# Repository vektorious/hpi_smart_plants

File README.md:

# Smart Plants Starter Kit

A hands-on introduction to building low-power, Wi-Fi-connected plant monitoring systems.
You'll learn the basics of microcontroller programming, soil moisture sensing, and Wi-Fi data
transfer — all while building a device that actually keeps your plants alive.

The device wakes from deep sleep, reads soil moisture (and optionally temperature, humidity,
light, and battery level), sends data to an online dashboard, then sleeps again to conserve
battery.

---

## What You'll Build

By the end of the workshop you'll have a battery-powered soil moisture sensor that:
- Measures soil moisture every hour (configurable)
- Sends data to an online dashboard via Wi-Fi
- Sleeps between measurements to conserve battery
- Waters your plant automatically when the soil gets too dry

No soldering experience required — but you'll get the chance to try!

---

## What's in the Kit

- Waveshare ESP32-C6 Zero microcontroller
- Smart Plants breakout PCB
- Capacitive soil moisture sensor + cable
- BME280 sensor (temperature, humidity, pressure)
- TSL2591 sensor (light)
- Mini diaphragm pump
- Battery pack
- Laser-cut housing
- 3D-printed sensor and pump housings
- Screws, velcro, cable gland

---

## Before You Begin

Make sure you have:
- A computer with a USB-C port (or adapter) and a **Chrome, Edge, or Opera** browser
  (used by the browser-based firmware installer)
- A USB-C **data** cable
- A 2.4 GHz Wi-Fi network

Everything else — firmware and configuration — is covered step by step in the build instructions
below. You install the firmware straight from the browser; only building it from source needs the
[Arduino IDE](https://www.arduino.cc/en/software).

---

## Build Instructions

**Start here:** [`instructions/build_instructions.md`](instructions/build_instructions.md)

That guide covers the full assembly, programming, calibration, and deployment for the main
Waveshare build — from soldering the PCB to seeing your first readings on the dashboard.

Firmware installs from the browser — no toolchain needed — via the web flasher:
**<https://vektorious.github.io/hpi_smart_plants/>**.

---

## Learning Goals

- Read analog sensor data and convert it to meaningful values
- Understand how to minimise power consumption with deep sleep
- Send data securely to a server over Wi-Fi using HTTP
- Learn how a cloud dashboard receives and displays live sensor readings

---

## Configured on the Device

All per-device settings — Wi-Fi, device name, sleep interval, moisture calibration, and
which sensors and the pump are enabled — are configured **on the device through a Wi-Fi setup
portal** after flashing, and stored in non-volatile memory. No code edits or recompiling: one
flashed binary works for every configuration.

The setup portal opens automatically on first boot (or on a double-press of the reset button) and
also shows **live sensor readings** and an **API connection test** so you can confirm everything
works. The `DEFAULT_*` values in `code/sp_modular/config.h` are only the factory defaults applied
on first boot. Building from source? See
[`instructions/firmware_from_source.md`](instructions/firmware_from_source.md).

---

## Board Variants

Two controller boards are supported. Both run the same firmware (`code/sp_modular/`).

| Variant | Board | PCB | Who it's for |
|---------|-------|-----|--------------|
| **Main build** | Waveshare ESP32-C6 Zero | `smart_plants_breakout_ws-board_rev2` | Student workshops |
| **Alternative** | SEEED Studio XIAO ESP32-C6 | `smart_plants_breakout_rev1` | Alternative / reference build |

---

## Repository Structure

```
code/
  sp_modular/              Modular firmware (current, for all builds)
    config.h               Factory defaults (DEFAULT_*), pin assignments, structs
    settings.ino           Runtime settings stored in NVS/Preferences
    portal.ino             WiFiManager setup portal + live sensor page
    sp_modular.ino         Entry point
    *.ino                  Sensor and actuator modules
  legacy/                  Old monolithic sketches (breadboard era, unsupported)

web-flasher/               Browser-based firmware installer (ESP Web Tools)

hardware/
  pcb/
    smart_plants_breakout_ws-board_rev2/   Main build PCB (Waveshare)
    smart_plants_breakout_rev1/            Alternative build PCB (XIAO)
    legacy/                                Older PCB revisions
    ext_files/                             KiCAD footprints and symbols
  3d-print/
    bme_housing/           Miniature Stevenson screen for BME280
    light_sensor/          TSL2591 mount with diffuser
    moisture_sensor/       Soil probe housing
    pump/                  Diaphragm pump enclosure
    cable_plugs/           M12 cable gland plug
  laser_files/
    SmartPlants_4mm_v3.svg Current enclosure template (4 mm material)
    legacy/                Older enclosure versions

instructions/
  build_instructions.md    Main build guide — start here
  firmware_from_source.md  Build/upload from Arduino IDE + component test sketches
  background_information.md Sensor theory, system overview, design rationale
  quick_reference/         Printable one-page build reference (md, html, pdf)
  legacy/                  Old breadboard-era guides (unsupported)

img/                       Photos and diagrams referenced by the instructions
```

---

## Background Reading

[`instructions/background_information.md`](instructions/background_information.md) covers:

- **Sensor selection** — why capacitive over resistive moisture sensors, why BME280 and TSL2591
  were chosen over simpler alternatives, and the trade-offs involved
- **Pump control** — how MOSFETs and relays work, and why this design uses an IRLZ14
- **How the system works** — the full data path from firmware wake-up cycle through the FastAPI
  server and PostgreSQL database to the live Grafana dashboard
- **Similar projects** — related open-source plant monitoring builds for further inspiration

Useful context for understanding *why* things are built the way they are.

---

## Licenses

| Component | License |
|-----------|---------|
| Software (`code/`) | [MIT](LICENSE.code) |
| Hardware (`hardware/`) | [CERN-OHL-W 2.0](LICENSE.hardware) |
| Documentation (`instructions/`, `README.md`, `img/`) | [CC-BY 4.0](LICENSE.docs) |

This project is certified open source hardware by OSHWA under certification ID `DE000173`.

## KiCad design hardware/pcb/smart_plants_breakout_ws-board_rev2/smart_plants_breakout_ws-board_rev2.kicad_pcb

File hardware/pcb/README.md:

# PCB Designs

Two active PCB designs are maintained, one per supported controller board. Both route sensors
to the same GPIO numbers, so no firmware changes are needed between variants.

## Active designs

### Waveshare ESP32-C6 Zero — `smart_plants_breakout_ws-board_rev2/` (main build)

The primary board used in student workshops. Designed for the
[Waveshare ESP32-C6 Zero](https://www.waveshare.com/wiki/ESP32-C6-Zero).

- **Gerber files:** `sp_ws_breakout_rev2/` folder and `sp_ws_breakout_rev2.zip`
- **KiCAD project:** `smart_plants_breakout_ws-board_rev2.kicad_pro`
- **Firmware pin config:** active block in `code/sp_modular/config.h`

### SEEED Studio XIAO ESP32-C6 — `smart_plants_breakout_rev1/` (alternative build)

Alternative build based on the [XIAO ESP32-C6](https://wiki.seeedstudio.com/xiao_esp32c6_getting_started/).

- **Gerber files:** `smart_plants_breakout_rev1_gerber/` folder and `smart_plants_breakout_rev1_gerber.zip`
- **KiCAD project:** `smart_plants_breakout_rev1.kicad_pro`
- **BOM:** `smart_plants_breakout_rev1.csv`
- **Firmware pin config:** see the commented-out XIAO block in `code/sp_modular/config.h` (TODO: GPIO numbers need to be verified)

## Ordering PCBs

1. Download the Gerber `.zip` file for your chosen variant.
2. Upload it to a PCB fab of your choice (e.g., JLCPCB, PCBWay, Aisler).
3. Default settings (1.6 mm FR4, 2 layers, HASL finish) work fine.

## Opening in KiCAD

Open the `.kicad_pro` file in KiCAD 8 or later. External footprint libraries are in
`ext_files/` — KiCAD will prompt you to resolve them on first open; point it to that folder.

## Legacy designs

Older PCB revisions are in `legacy/`. They are archived for reference only.

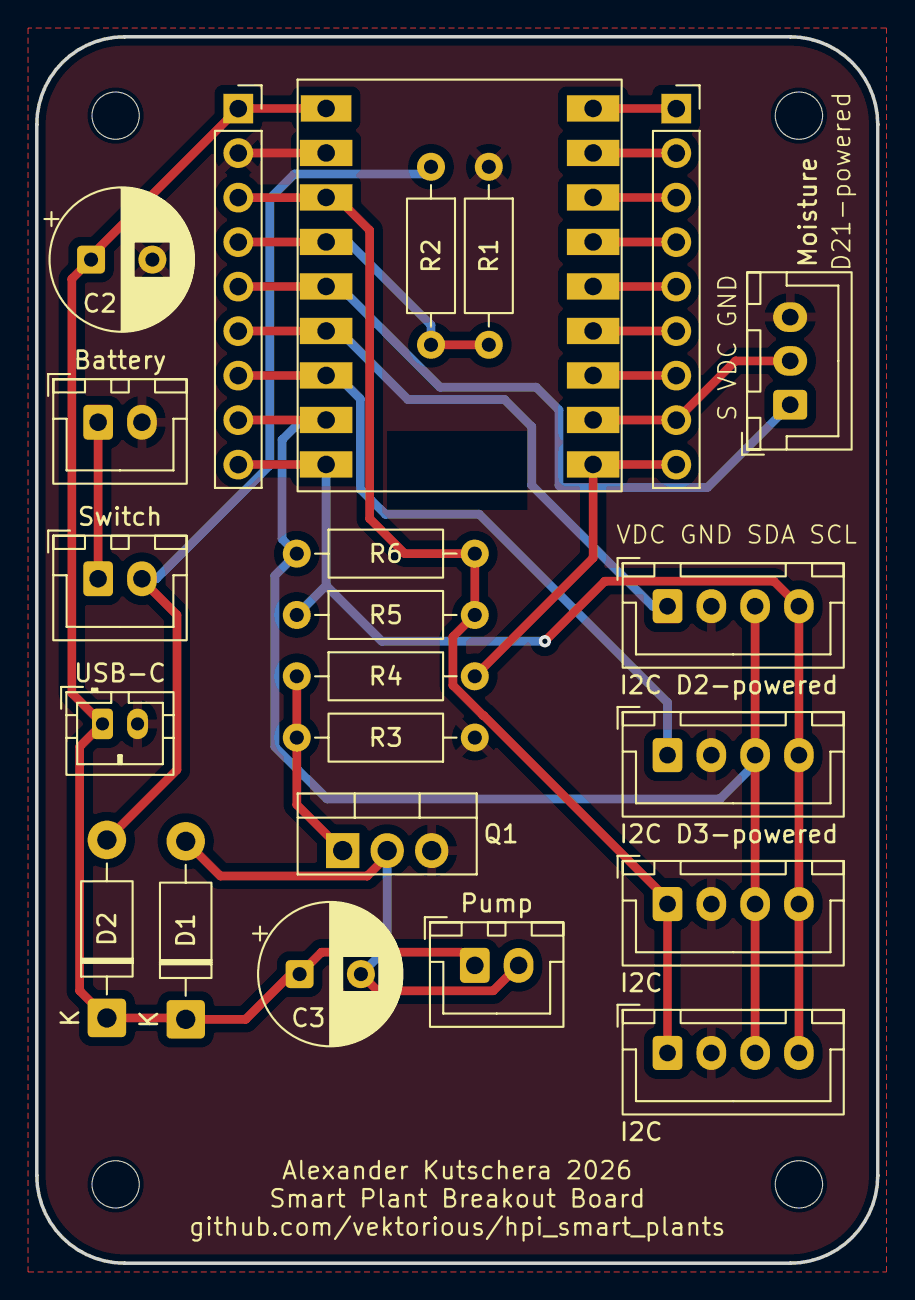
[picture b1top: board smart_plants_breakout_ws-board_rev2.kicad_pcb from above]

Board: 2 copper layers, 48.0 x 70.0 mm, 27 parts (0 on the bottom side), 22 nets.

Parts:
Battery: Battery; JST_XH_B2B-XH-A_1x02_P2.50mm_Vertical
C2: 220µF; CP_Radial_D8.0mm_P3.50mm
C3: 22µF; CP_Radial_D8.0mm_P3.50mm
D1: 1N4001; D_DO-41_SOD81_P10.16mm_Horizontal
D2: 1N5817; D_DO-41_SOD81_P10.16mm_Horizontal
H1, H2, H3, H4: MountingHole; MountingHole_2.7mm_M2.5
I2C, I2C#2: I2C; JST_XH_B4B-XH-A_1x04_P2.50mm_Vertical
I2C D2-powered: I2C D2-powered; JST_XH_B4B-XH-A_1x04_P2.50mm_Vertical
I2C D3-powered: I2C D3-powered; JST_XH_B4B-XH-A_1x04_P2.50mm_Vertical
J1, J2: Conn_01x09_Pin; PinSocket_1x09_P2.54mm_Vertical
Moisture: Moisture Sensor; JST_XH_B3B-XH-A_1x03_P2.50mm_Vertical
Pump: Pump; JST_XH_B2B-XH-A_1x02_P2.50mm_Vertical
Q1: IRLZ14; TO-220-3_Vertical
R1, R2: 220k; R_Axial_DIN0207_L6.3mm_D2.5mm_P10.16mm_Horizontal
R3: 10k; R_Axial_DIN0207_L6.3mm_D2.5mm_P10.16mm_Horizontal
R4: 22R; R_Axial_DIN0207_L6.3mm_D2.5mm_P10.16mm_Horizontal
R5, R6: 4k7; R_Axial_DIN0207_L6.3mm_D2.5mm_P10.16mm_Horizontal
Switch: Power Switch; JST_XH_B2B-XH-A_1x02_P2.50mm_Vertical
U1: Waveshare ESP32-C6-Nano; Waveshare-ESP32-C6-Zero-THT
USB-C: USB-C Power; JST_PH_B2B-PH-K_1x02_P2.00mm_Vertical

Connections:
GND: Battery.2, C2.2, I2C.2, I2C D2-powered.2, I2C D3-powered.2, I2C#2.2, J1.2, Moisture.3, Q1.3 (S), R1.1, R3.1, U1.2 (GND), USB-C.2
unnamed: C3.2, D1.2 (A), Pump.2, Q1.2 (D)
unnamed: C2.1, C3.1, D1.1 (K), D2.1 (K), J1.1, Pump.1, U1.1 (VCC), USB-C.1
unnamed: D2.2 (A), R2.1, Switch.2 (B)
unnamed: J1.4, R1.2, R2.2, U1.4 (IO0)
unnamed: J1.5, Moisture.1, U1.5 (IO1)
unnamed: I2C D2-powered.1, J1.6, U1.6 (IO2)
unnamed: I2C D3-powered.1, J1.7, U1.7 (IO3)
unnamed: I2C.3, I2C D2-powered.3, I2C D3-powered.3, I2C#2.3, J1.8, R6.1, U1.8 (IO4)
unnamed: I2C.4, I2C D2-powered.4, I2C D3-powered.4, I2C#2.4, J1.9, R5.1, U1.9 (IO5)
unnamed: J2.1, U1.18 (TX)
unnamed: J2.2, U1.17 (RX)
unnamed: J2.3, U1.16 (IO14)
unnamed: J2.4, U1.15 (IO15)
unnamed: J2.5, U1.14 (IO18)
unnamed: J2.6, U1.13 (IO19)
unnamed: J2.7, U1.12 (IO20)
unnamed: J2.8, Moisture.2, U1.11 (IO21)
unnamed: J2.9, R4.2, U1.10 (IO22)
unnamed: Battery.1, Switch.1 (A)
unnamed: Q1.1 (G), R3.2, R4.1
VDC: I2C.1, I2C#2.1, J1.3, R5.2, R6.2, U1.3 (V3V)

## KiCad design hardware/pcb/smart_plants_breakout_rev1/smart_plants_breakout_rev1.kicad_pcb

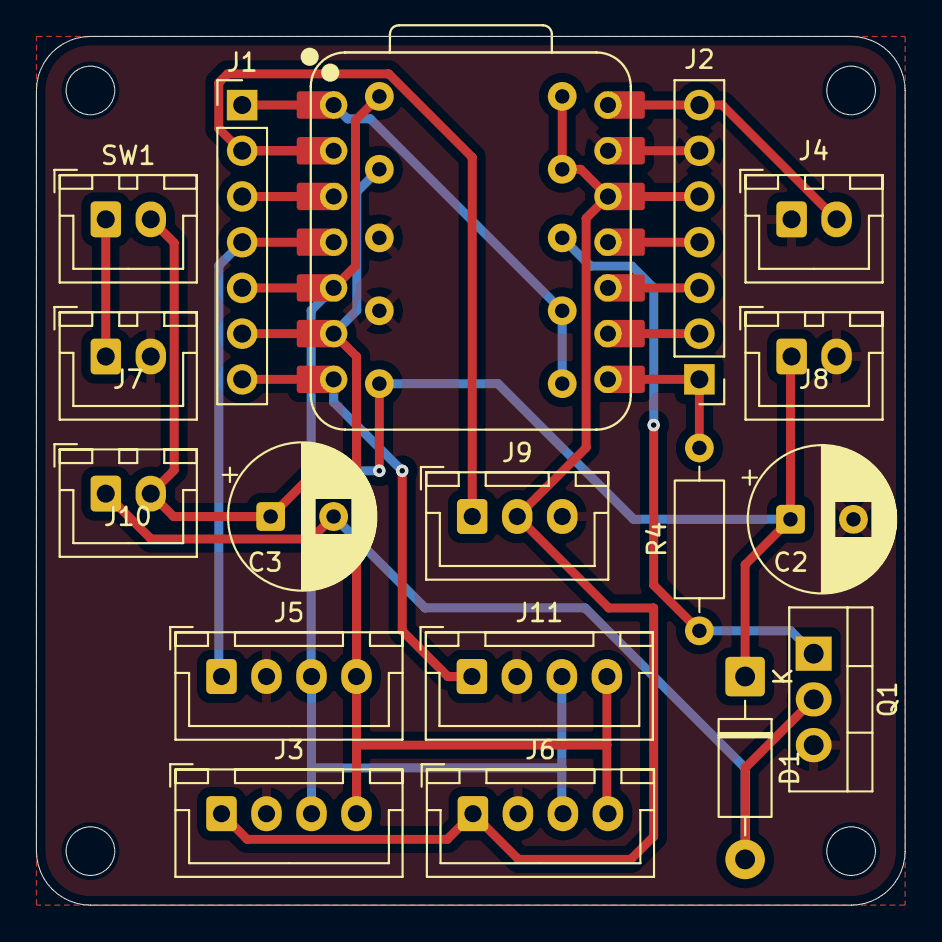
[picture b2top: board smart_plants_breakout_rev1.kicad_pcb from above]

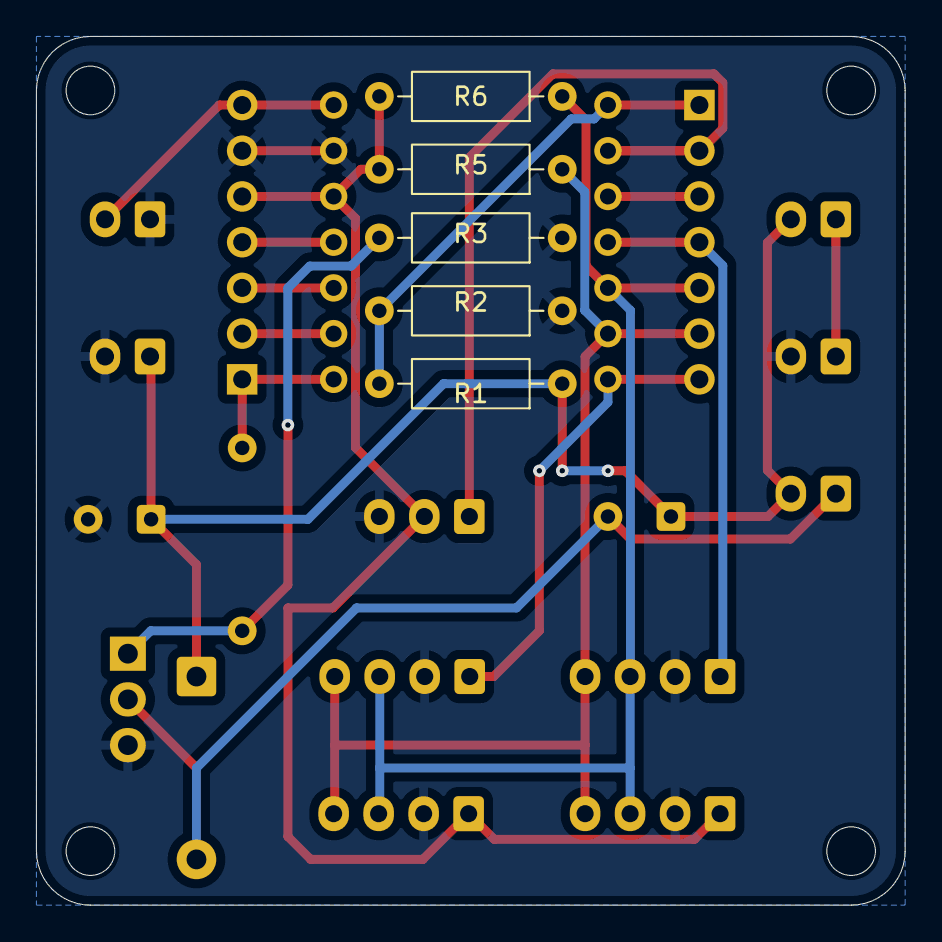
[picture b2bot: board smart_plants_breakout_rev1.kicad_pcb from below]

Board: 2 copper layers, 48.3 x 48.3 mm, 27 parts (5 on the bottom side), 18 nets.

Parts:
C2: 220µF; CP_Radial_D8.0mm_P3.50mm
C3: 22µF; CP_Radial_D8.0mm_P3.50mm
D1: 1N4001; D_DO-41_SOD81_P10.16mm_Horizontal
H1, H2, H3, H4: MountingHole; MountingHole_2.7mm_M2.5
J1, J2: Breakout; PinHeader_1x07_P2.54mm_Vertical
J3, J6: I2C; JST_XH_B4B-XH-A_1x04_P2.50mm_Vertical
J4: USB-C Power; JST_XH_B2B-XH-A_1x02_P2.50mm_Vertical
J5: I2C D3-powered; JST_XH_B4B-XH-A_1x04_P2.50mm_Vertical
J7: Battery; JST_XH_B2B-XH-A_1x02_P2.50mm_Vertical
J8: Board Power; JST_XH_B2B-XH-A_1x02_P2.50mm_Vertical
J9: Moisture Sensor; JST_XH_B3B-XH-A_1x03_P2.50mm_Vertical
J10: Pump; JST_XH_B2B-XH-A_1x02_P2.50mm_Vertical
J11: I2C D6-powered; JST_XH_B4B-XH-A_1x04_P2.50mm_Vertical
Q1: IRLZ14; TO-220-3_Vertical
R1, R2: 220k; R_Axial_DIN0207_L6.3mm_D2.5mm_P10.16mm_Horizontal
R3: 10k; R_Axial_DIN0207_L6.3mm_D2.5mm_P10.16mm_Horizontal
R4: 22R; R_Axial_DIN0207_L6.3mm_D2.5mm_P10.16mm_Horizontal
R5, R6: 4k7; R_Axial_DIN0207_L6.3mm_D2.5mm_P10.16mm_Horizontal
SW1: Power Switch; JST_XH_B2B-XH-A_1x02_P2.50mm_Vertical
U1: XIAO-ESP32-C6; XIAO-ESP32C6-DIP

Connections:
BAT+: C2.1, C3.1, D1.1 (K), J8.1, J10.2, R1.1, SW1.2 (B)
BAT-: C2.2, J2.6, J3.2, J4.1, J5.2, J6.2, J7.2, J8.2, J9.3, J11.2, Q1.3 (S), R2.1, R3.1, U1.13 (GND)
unnamed: C3.2, D1.2 (A), J10.1, Q1.2 (D)
unnamed: J1.1, R1.2, R2.2, U1.1 (GPIO0/A0/D0)
unnamed: J1.2, J9.1, U1.2 (GPIO1/A1/D1)
unnamed: J1.3, U1.3 (GPIO2/A2/D2)
unnamed: J1.4, J5.1, U1.4 (GPIO21/D3)
unnamed: J1.5, J3.3, J5.3, J6.3, J11.3, R6.1, U1.5 (GPIO22/D4/SDA)
unnamed: J1.6, J3.4, J5.4, J6.4, J11.4, R5.1, U1.6 (GPIO23/D5/SCL)
unnamed: J1.7, J11.1, U1.7 (GPIO16/D6/TX)
unnamed: J2.1, R4.2, U1.8 (GPIO17/D7/RX)
unnamed: J2.2, U1.9 (GPIO19/D8/SCK)
unnamed: J2.3, U1.10 (GPIO20/D9/MISO)
unnamed: J2.4, U1.11 (GPIO18/D10/MOSI)
unnamed: J7.1, SW1.1 (A)
unnamed: Q1.1 (G), R3.2, R4.1
VBUS: J2.7, J4.2, U1.14 (VBUS)
VDC: J2.5, J3.1, J6.1, J9.2, R5.2, R6.2, U1.12 (3V3)

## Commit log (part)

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2025-09-18 Adds build instructions and images
    Adds a comprehensive instructions document detailing the steps to assemble the moisture sensor project, including preparation, circuit assembly, programming, and final testing.
    Includes associated images for each step to aid visual understanding.
2025-09-18 Updates images and adds spacing for clarity
    Improves the visual presentation of the assembly instructions.
    Adds spacing between steps for better readability and increases the size of circuit diagrams for improved clarity.
2025-09-18 Refactors instructions for clarity.
    Improves the instructions document by:
    - Adjusting the formatting of image elements for better layout.
    - Restructuring titles for better organization and readability.
2025-09-18 Refractors instructions, adds ESP32 board pinout
2025-09-18 Adds initial project files and instructions
    Initializes the "Smart Plants Starter Kit" project with a README,
    instructions, and an image of the ESP32-C6 pinout.
    The project provides a hands-on introduction to building a low-power,
    Wi-Fi-connected plant monitoring system.
    Uses a local image for the ESP32-C6 pinout in the instructions.
2025-09-18 Uploaded first script
2025-09-23 Adds WiFi Manager for configuration
    Implements WiFi Manager to allow for easy configuration
    of the WiFi connection via a web interface if the device
    is unable to connect using the stored credentials.
    Also refactors the WiFi connection logic into its own function.
2025-09-24 Updated instructions
2025-11-18 Adds 3D-models
2025-11-18 Adds files for the laser cutter
2025-11-18 Adds PCB breakout design files
2025-11-18 fixed error in 3D-design
2025-11-18 Added code samples
2025-11-18 Fixed errors in the fritzing layouts and added new ones
2025-11-18 added circuit exports
2025-11-18 Added 3D-files and Attribution
2025-11-18 updated BOM
2025-11-18 updated img paths
2025-12-10 Added new code sketch
2026-03-06 Added PCB
2026-04-07 WS PCB bug fixes
2026-04-07 WS PCB rev2
2026-04-20 added new housing files
2026-04-22 minor improvements in housing files
2026-04-22 fix: apply code review improvements to sp_modular firmware
    - Remove hasAnyData guard that prevented data from being sent when
    optional sensors are disabled (#3)
    - Add moisture_voltage field to JSON payload (#9)
    - Power off BME280 and TSL2591 after reading to save battery (#4)
    - Move Wire.begin() to setup() and guard it with feature flags (#5)
    - Add warm-up ADC read for battery voltage to discard noisy first
2026-04-22 reodering 3D-print files
2026-04-22 moving light sensor file
2026-04-23 fix: send light sensor data when lux/IR are 0 at night
    calculateLux(0, 0) produced NaN due to internal division by zero,
    causing lux to be filtered out by isValidFloat(). The ir/full guard
    `d.ir > 0 || d.full > 0` also blocked valid zero readings.
    Fix: short-circuit calculateLux for all-zero readings, initialize
    d.lux to NAN so sensor failure is distinguishable, and gate ir/full
    on lux validity instead of a nonzero check.
2026-04-24 changed pins
2026-04-24 fix(tsl2591): re-init Wire with correct pins before begin(), add I2C scan debug
    Adafruit_I2CDevice::begin() calls Wire.begin() internally without
    parameters, which on ESP32 may reset SDA/SCL to default pins and
    override the Wire.begin(PIN_SDA, PIN_SCL) set in setup(). Re-calling
    Wire.begin with explicit pins in readTSL() guards against this.
    Added I2C bus scan and pin printout before tsl.begin() to give
    actionable Serial output when the sensor is not found.
2026-04-24 fixed TSL bug manually, Caude was to stupid
2026-04-24 Reworked licensing
2026-04-24 resized cert size
2026-04-28 refactoring
2026-04-28 added new cable_plugs
2026-04-28 added OSHWA ID to the housing
2026-04-29 fixed wm connection bug
2026-05-18 updated PCB files
2026-06-25 added dedicated BOMs
2026-06-26 updated BOMs
